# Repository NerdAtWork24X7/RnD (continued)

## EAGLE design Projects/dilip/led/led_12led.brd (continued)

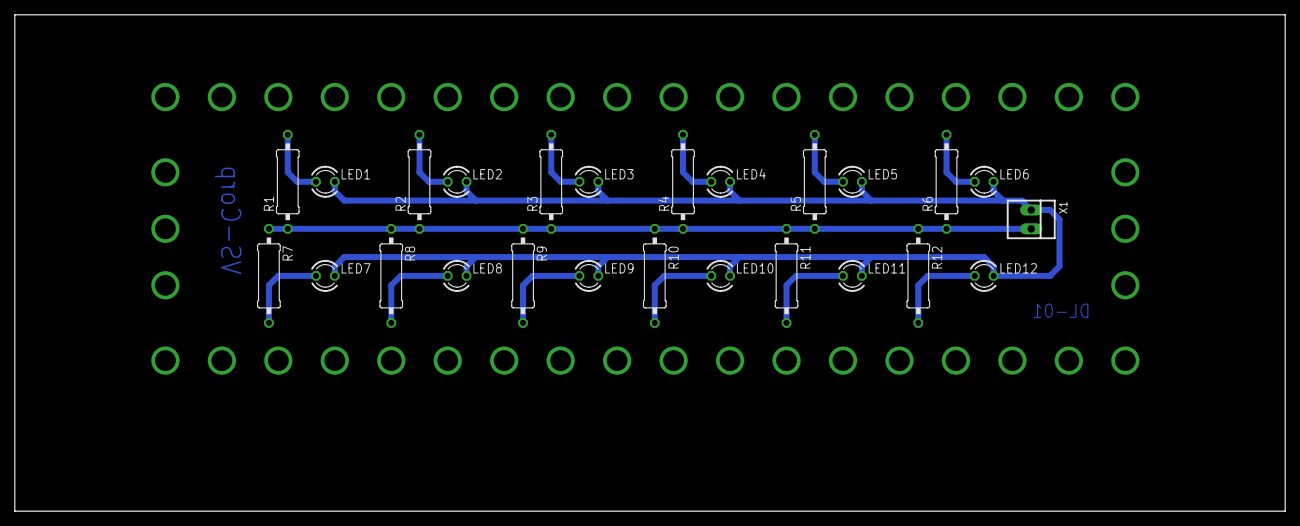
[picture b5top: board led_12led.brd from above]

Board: 2 copper layers, 171.4 x 67.0 mm, 25 parts (0 on the bottom side), 14 nets.

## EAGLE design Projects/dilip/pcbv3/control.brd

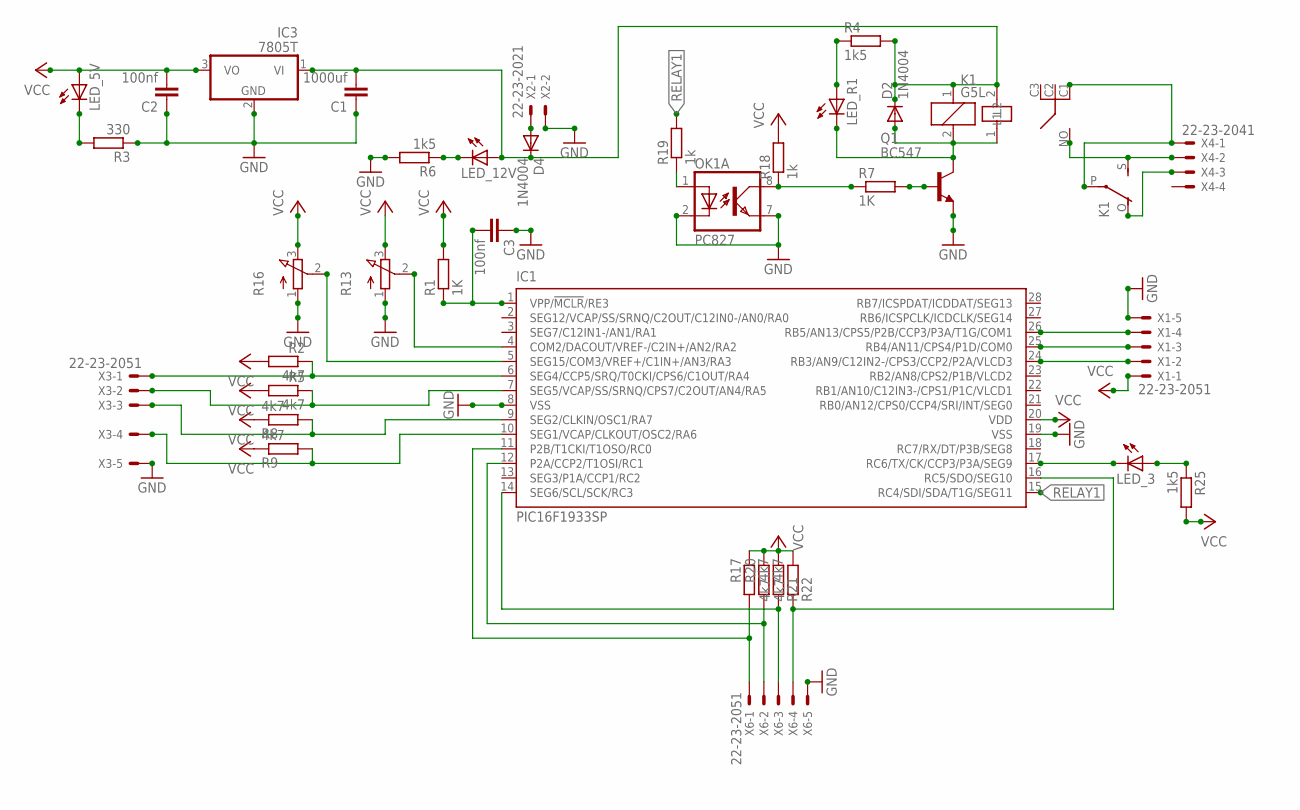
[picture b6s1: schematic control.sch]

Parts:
C1: 1000uf; C5B2.5
C2, C3: 100nf; C2.5-6
D2, D4: 1N4004; DO41-10
IC1: PIC16F1933SP; DIL28-3
IC3: 7805T; TO220H
K1: G5L; G5LE
LED_3, LED_5V, LED_12V: LED3MM
LED_R1: LED3MM
OK1: PC827; DIL08
Q1: BC547; TO92-EBC
R1, R7: 1K; 0207/10
R2, R5, R8, R9, R17, R20, R21, R22: 4k7; 0207/10
R3: 330; 0207/10
R4, R6, R25: 1k5; 0207/10
R13, R16: 3RP/1610N
R18, R19: 1k; 0207/10
U$1: RL703
X1, X3, X6: 22-23-2051
X2: 22-23-2021
X4: 22-23-2041

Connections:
GND: C1.1, C2.1, C3.1, IC1.8 (VSS), IC1.19 (VSS), IC3.2 (GND), OK1.2 (C), OK1.7 (EMIT), Q1.E, R3.1, R6.2, R13.1 (A), R16.1 (A), X1.5, X2.2, X3.5, X6.5
unnamed: IC1.7 (SEG5/VCAP/SS/SRNQ/CPS7/C2OUT/AN4/RA5), R5.1, X3.2
unnamed: C3.2, IC1.1 (VPP/!MCLR!/RE3), R1.1
unnamed: IC1.4 (COM2/DACOUT/VREF-/C2IN+/AN2/RA2), R13.2 (S)
unnamed: IC1.5 (SEG15/COM3/VREF+/C1IN+/AN3/RA3), R16.2 (S)
unnamed: IC1.25 (RB4/AN11/CPS4/P1D/COM0), X1.3
unnamed: IC1.6 (SEG4/CCP5/SRQ/T0CKI/CPS6/C1OUT/RA4), R2.1, X3.1
unnamed: IC1.9 (SEG2/CLKIN/OSC1/RA7), R8.2, X3.3
unnamed: IC1.10 (SEG1/VCAP/CLKOUT/OSC2/RA6), R9.2, X3.4
unnamed: IC1.14 (SEG6/SCL/SCK/RC3), R21.1, X6.3
unnamed: Q1.B, R7.2
unnamed: D2.A, K1.2, LED_R1.K (C), Q1.C, U$1.1 (L2)
unnamed: IC1.11 (P2B/T1CKI/T1OSO/RC0), R17.2, X6.1
unnamed: IC1.24 (RB3/AN9/C12IN2-/CPS3/CCP2/P2A/VLCD3), X1.2
unnamed: IC1.12 (P2A/CCP2/T1OSI/RC1), R20.2, X6.2
unnamed: K1.S, U$1.NO, X4.2
unnamed: K1.P, U$1.C1, X4.1
unnamed: K1.O, X4.3
unnamed: D4.A, X2.1
unnamed: LED_5V.K (C), R3.2
unnamed: IC1.26 (RB5/AN13/CPS5/P2B/CCP3/P3A/T1G/COM1), X1.4
unnamed: LED_R1.A, R4.1
unnamed: LED_12V.K (C), R6.1
unnamed: C1.2, D2.C, D4.C, IC3.1 (VI), K1.1, LED_12V.A, R4.2, U$1.2 (L1)
unnamed: OK1.8 (COL), R7.1, R18.1
unnamed: OK1.1 (A), R19.1
unnamed: IC1.16 (RC5/SDO/SEG10), R22.1, X6.4
unnamed: LED_3.A, R25.1
unnamed: IC1.17 (RC6/TX/CK/CCP3/P3A/SEG9), LED_3.K (C)
RELAY1: IC1.15 (RC4/SDI/SDA/T1G/SEG11), R19.2
VCC: C2.2, IC1.20 (VDD), IC3.3 (VO), LED_5V.A, R1.2, R2.2, R5.2, R8.1, R9.1, R13.3 (E), R16.3 (E), R17.1, R18.2, R20.1, R21.2, R22.2, R25.2, X1.1

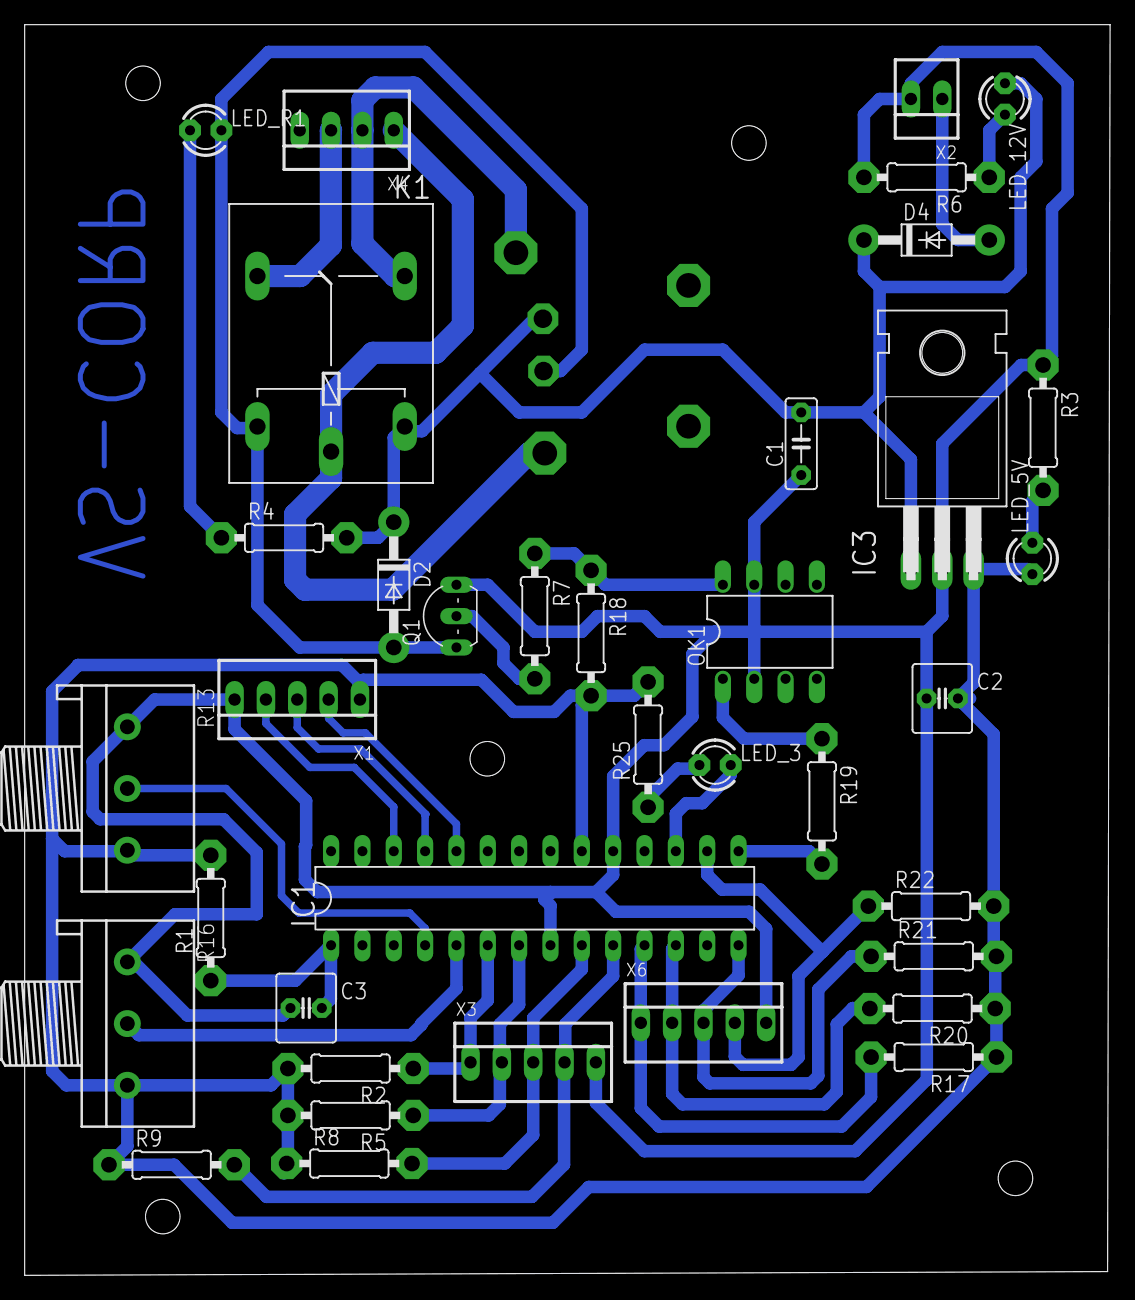
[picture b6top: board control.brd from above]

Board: 2 copper layers, 88.0 x 101.3 mm, 38 parts (0 on the bottom side), 31 nets.

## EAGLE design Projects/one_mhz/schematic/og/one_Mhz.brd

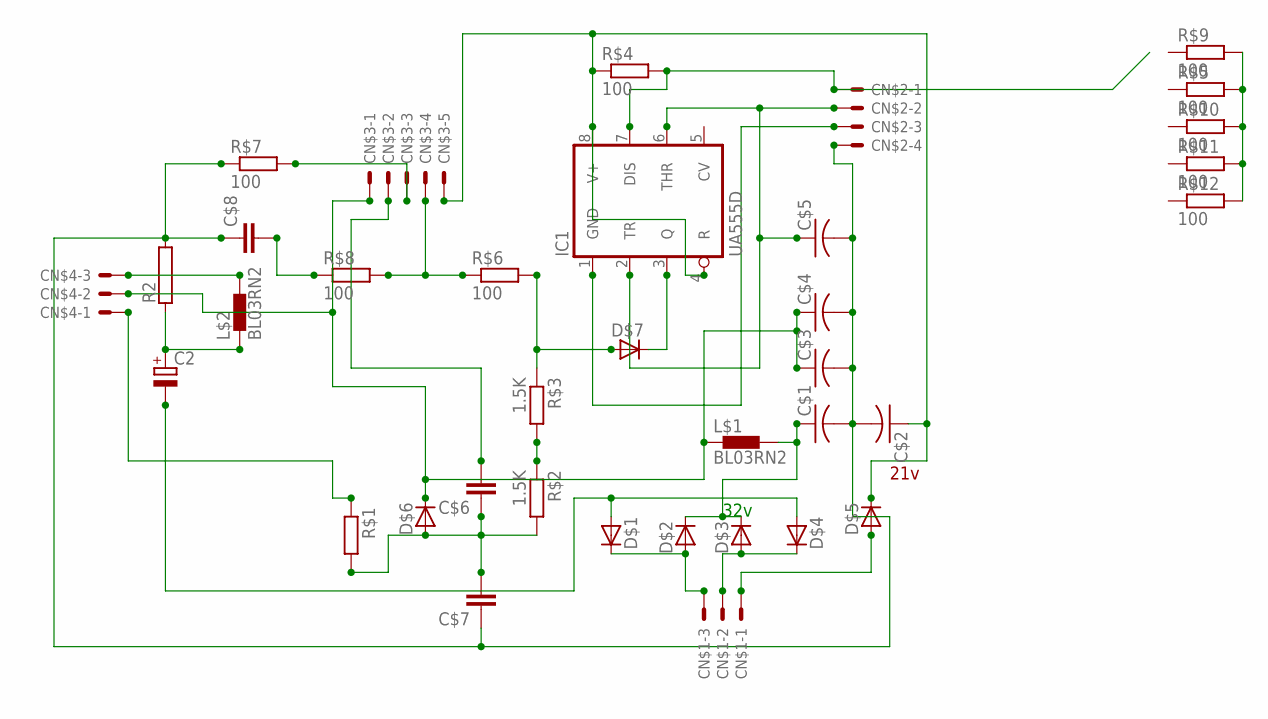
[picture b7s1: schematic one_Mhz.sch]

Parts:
C2: CPOL-EUSANYO_H; SANYO-OSCON_H
C$1, C$2: C-US050-075X075; C050-075X075
C$3, C$4, C$5: C-US025-050X050; C025-050X050
C$6, C$7: C7.5/3; C7.5B3
C$8: C2.5/5; C2.5-5
CN$1, CN$4: KK-156-3
CN$2: KK-156-4
CN$3: KK-156-5
D$1, D$2, D$3, D$4, D$5, D$6, D$7: D-SOD-87; SOD87
IC1: UA555D; SO08
L$1, L$2: BL03RN2
R2: RAC01; AC01
R$1: R-EU_R0603; R0603
R$2, R$3: 1.5K; R0603
R$4, R$5, R$6, R$7, R$8, R$9, R$10, R$11, R$12: 100; R0603

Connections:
unnamed: C$3.1, C$4.1, CN$3.1, CN$4.2, D$6.1 (C), L$1.1
unnamed: CN$1.2, D$3.2 (A), D$4.1 (C)
unnamed: CN$1.3, D$1.1 (C), D$2.2 (A)
unnamed: C2.-, D$1.2 (A), D$4.2 (A)
unnamed: CN$1.1, D$5.2 (A)
unnamed: C$1.2, C$2.2, C$3.2, C$4.2, C$5.2, C$7.1, C$8.1, CN$2.4, R2.2, R$7.1
unnamed: R$2.1, R$3.2
unnamed: D$7.2 (A), R$3.1, R$6.2
unnamed: D$7.1 (C), IC1.3 (Q)
unnamed: CN$3.4, R$6.1, R$8.2
unnamed: C$8.2, R$8.1
unnamed: C$5.1, CN$2.2, IC1.2 (TR), IC1.6 (THR)
unnamed: CN$3.3, R$7.2
unnamed: CN$4.3, L$2.2
unnamed: C2.+, L$2.1, R2.1
unnamed: R$5.2, R$9.2, R$10.2, R$11.2, R$12.2
unnamed: C$6.2, CN$3.2
unnamed: C$6.1, C$7.2, D$6.2 (A), R$1.2, R$2.2
unnamed: C$1.1, D$2.1 (C), D$3.1 (C), L$1.2
unnamed: C$2.1, CN$3.5, D$5.1 (C), IC1.4 (R), IC1.8 (V+), R$4.1
unnamed: CN$4.1, R$1.1
unnamed: CN$2.1, IC1.7 (DIS), R$4.2
unnamed: CN$2.3, IC1.1 (GND)

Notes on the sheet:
21v
32v

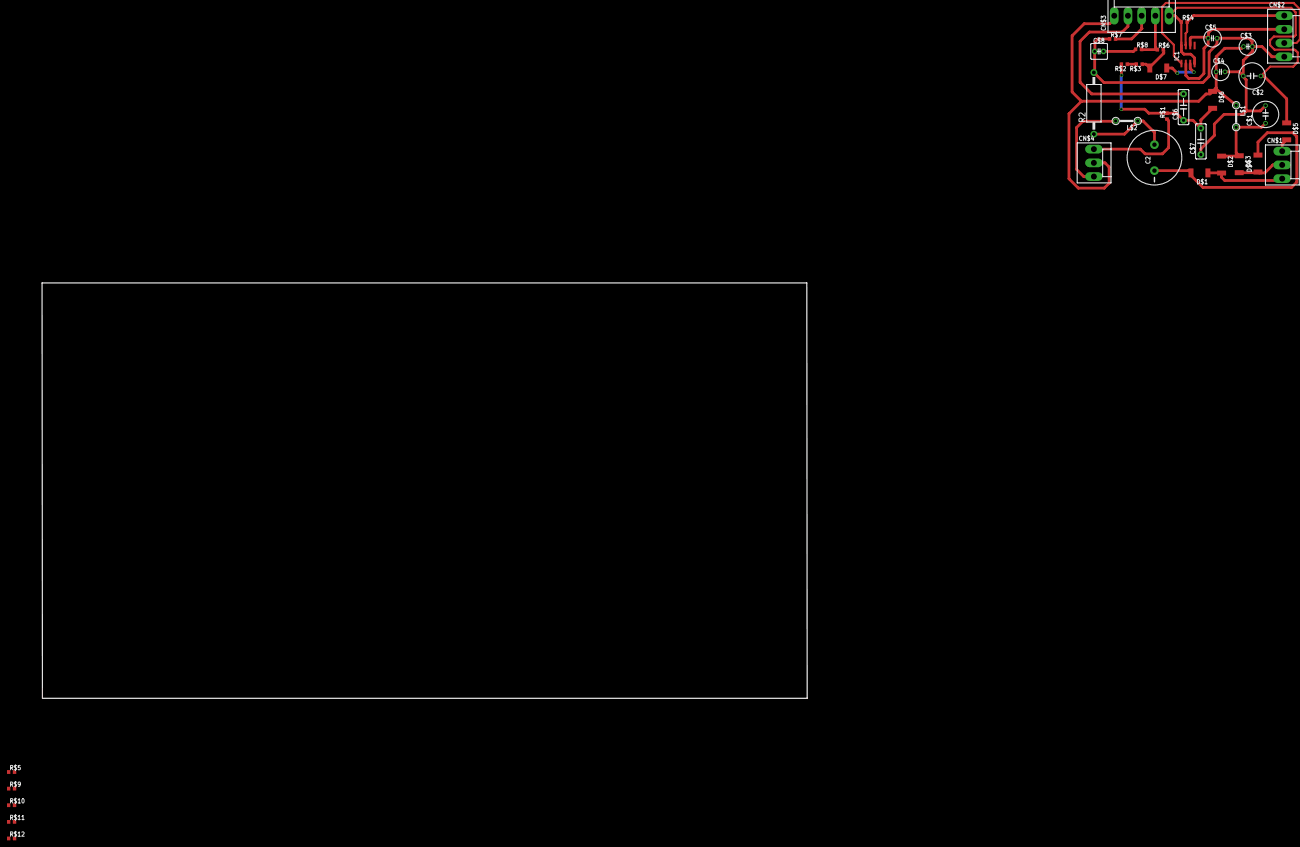
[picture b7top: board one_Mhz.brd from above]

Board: 2 copper layers, 36 parts (0 on the bottom side), 23 nets.

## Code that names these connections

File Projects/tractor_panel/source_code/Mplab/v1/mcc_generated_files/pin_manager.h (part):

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// get/set channel_AN0 aliases
#define channel_AN0_TRIS                 TRISAbits.TRISA0
#define channel_AN0_LAT                  LATAbits.LATA0
#define channel_AN0_PORT                 PORTAbits.RA0
#define channel_AN0_ANS                  ANCON0bits.ANSEL0
#define channel_AN0_SetHigh()            do { LATAbits.LATA0 = 1; } while(0)
#define channel_AN0_SetLow()             do { LATAbits.LATA0 = 0; } while(0)
#define channel_AN0_Toggle()             do { LATAbits.LATA0 = ~LATAbits.LATA0; } while(0)
#define channel_AN0_GetValue()           PORTAbits.RA0
#define channel_AN0_SetDigitalInput()    do { TRISAbits.TRISA0 = 1; } while(0)
#define channel_AN0_SetDigitalOutput()   do { TRISAbits.TRISA0 = 0; } while(0)
#define channel_AN0_SetAnalogMode()      do { ANCON0bits.ANSEL0 = 1; } while(0)
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// get/set channel_AN1 aliases
#define channel_AN1_TRIS                 TRISAbits.TRISA1
#define channel_AN1_LAT                  LATAbits.LATA1
#define channel_AN1_PORT                 PORTAbits.RA1
#define channel_AN1_ANS                  ANCON0bits.ANSEL1
#define channel_AN1_SetHigh()            do { LATAbits.LATA1 = 1; } while(0)
#define channel_AN1_SetLow()             do { LATAbits.LATA1 = 0; } while(0)
#define channel_AN1_Toggle()             do { LATAbits.LATA1 = ~LATAbits.LATA1; } while(0)
#define channel_AN1_GetValue()           PORTAbits.RA1
#define channel_AN1_SetDigitalInput()    do { TRISAbits.TRISA1 = 1; } while(0)
#define channel_AN1_SetDigitalOutput()   do { TRISAbits.TRISA1 = 0; } while(0)
#define channel_AN1_SetAnalogMode()      do { ANCON0bits.ANSEL1 = 1; } while(0)
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// get/set channel_AN2 aliases
#define channel_AN2_TRIS                 TRISAbits.TRISA2
#define channel_AN2_LAT                  LATAbits.LATA2
#define channel_AN2_PORT                 PORTAbits.RA2
#define channel_AN2_ANS                  ANCON0bits.ANSEL2
#define channel_AN2_SetHigh()            do { LATAbits.LATA2 = 1; } while(0)
#define channel_AN2_SetLow()             do { LATAbits.LATA2 = 0; } while(0)
#define channel_AN2_Toggle()             do { LATAbits.LATA2 = ~LATAbits.LATA2; } while(0)
#define channel_AN2_GetValue()           PORTAbits.RA2
#define channel_AN2_SetDigitalInput()    do { TRISAbits.TRISA2 = 1; } while(0)
#define channel_AN2_SetDigitalOutput()   do { TRISAbits.TRISA2 = 0; } while(0)
#define channel_AN2_SetAnalogMode()      do { ANCON0bits.ANSEL2 = 1; } while(0)
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// get/set channel_AN3 aliases
#define channel_AN3_TRIS                 TRISAbits.TRISA3
#define channel_AN3_LAT                  LATAbits.LATA3
#define channel_AN3_PORT                 PORTAbits.RA3
#define channel_AN3_ANS                  ANCON0bits.ANSEL3
#define channel_AN3_SetHigh()            do { LATAbits.LATA3 = 1; } while(0)
#define channel_AN3_SetLow()             do { LATAbits.LATA3 = 0; } while(0)
#define channel_AN3_Toggle()             do { LATAbits.LATA3 = ~LATAbits.LATA3; } while(0)
#define channel_AN3_GetValue()           PORTAbits.RA3
#define channel_AN3_SetDigitalInput()    do { TRISAbits.TRISA3 = 1; } while(0)
#define channel_AN3_SetDigitalOutput()   do { TRISAbits.TRISA3 = 0; } while(0)
#define channel_AN3_SetAnalogMode()      do { ANCON0bits.ANSEL3 = 1; } while(0)
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// get/set channel_AN4 aliases
#define channel_AN4_TRIS                 TRISAbits.TRISA5
#define channel_AN4_LAT                  LATAbits.LATA5
#define channel_AN4_PORT                 PORTAbits.RA5
#define channel_AN4_ANS                  ANCON0bits.ANSEL4
#define channel_AN4_SetHigh()            do { LATAbits.LATA5 = 1; } while(0)
#define channel_AN4_SetLow()             do { LATAbits.LATA5 = 0; } while(0)
#define channel_AN4_Toggle()             do { LATAbits.LATA5 = ~LATAbits.LATA5; } while(0)
#define channel_AN4_GetValue()           PORTAbits.RA5
#define channel_AN4_SetDigitalInput()    do { TRISAbits.TRISA5 = 1; } while(0)
#define channel_AN4_SetDigitalOutput()   do { TRISAbits.TRISA5 = 0; } while(0)
#define channel_AN4_SetAnalogMode()      do { ANCON0bits.ANSEL4 = 1; } while(0)
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// get/set IO_RB0 aliases
#define IO_RB0_TRIS                 TRISBbits.TRISB0
#define IO_RB0_LAT                  LATBbits.LATB0
#define IO_RB0_PORT                 PORTBbits.RB0
#define IO_RB0_WPU                  WPUBbits.WPUB0
#define IO_RB0_ANS                  ANCON1bits.ANSEL10
#define IO_RB0_SetHigh()            do { LATBbits.LATB0 = 1; } while(0)
#define IO_RB0_SetLow()             do { LATBbits.LATB0 = 0; } while(0)
#define IO_RB0_Toggle()             do { LATBbits.LATB0 = ~LATBbits.LATB0; } while(0)
#define IO_RB0_GetValue()           PORTBbits.RB0
#define IO_RB0_SetDigitalInput()    do { TRISBbits.TRISB0 = 1; } while(0)
#define IO_RB0_SetDigitalOutput()   do { TRISBbits.TRISB0 = 0; } while(0)
#define IO_RB0_SetPullup()          do { WPUBbits.WPUB0 = 1; } while(0)
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// get/set IO_RB1 aliases
#define IO_RB1_TRIS                 TRISBbits.TRISB1
#define IO_RB1_LAT                  LATBbits.LATB1
#define IO_RB1_PORT                 PORTBbits.RB1
#define IO_RB1_WPU                  WPUBbits.WPUB1
#define IO_RB1_ANS                  ANCON1bits.ANSEL8
#define IO_RB1_SetHigh()            do { LATBbits.LATB1 = 1; } while(0)
#define IO_RB1_SetLow()             do { LATBbits.LATB1 = 0; } while(0)
#define IO_RB1_Toggle()             do { LATBbits.LATB1 = ~LATBbits.LATB1; } while(0)
#define IO_RB1_GetValue()           PORTBbits.RB1
#define IO_RB1_SetDigitalInput()    do { TRISBbits.TRISB1 = 1; } while(0)
#define IO_RB1_SetDigitalOutput()   do { TRISBbits.TRISB1 = 0; } while(0)
#define IO_RB1_SetPullup()          do { WPUBbits.WPUB1 = 1; } while(0)
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// get/set IO_RB2 aliases
#define IO_RB2_TRIS                 TRISBbits.TRISB2
#define IO_RB2_LAT                  LATBbits.LATB2
#define IO_RB2_PORT                 PORTBbits.RB2
#define IO_RB2_WPU                  WPUBbits.WPUB2
#define IO_RB2_SetHigh()            do { LATBbits.LATB2 = 1; } while(0)
#define IO_RB2_SetLow()             do { LATBbits.LATB2 = 0; } while(0)
#define IO_RB2_Toggle()             do { LATBbits.LATB2 = ~LATBbits.LATB2; } while(0)
#define IO_RB2_GetValue()           PORTBbits.RB2
#define IO_RB2_SetDigitalInput()    do { TRISBbits.TRISB2 = 1; } while(0)
#define IO_RB2_SetDigitalOutput()   do { TRISBbits.TRISB2 = 0; } while(0)
#define IO_RB2_SetPullup()          do { WPUBbits.WPUB2 = 1; } while(0)
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// get/set IO_RB3 aliases
#define IO_RB3_TRIS                 TRISBbits.TRISB3
#define IO_RB3_LAT                  LATBbits.LATB3
#define IO_RB3_PORT                 PORTBbits.RB3
#define IO_RB3_WPU                  WPUBbits.WPUB3
#define IO_RB3_SetHigh()            do { LATBbits.LATB3 = 1; } while(0)
#define IO_RB3_SetLow()             do { LATBbits.LATB3 = 0; } while(0)
#define IO_RB3_Toggle()             do { LATBbits.LATB3 = ~LATBbits.LATB3; } while(0)
#define IO_RB3_GetValue()           PORTBbits.RB3
#define IO_RB3_SetDigitalInput()    do { TRISBbits.TRISB3 = 1; } while(0)
#define IO_RB3_SetDigitalOutput()   do { TRISBbits.TRISB3 = 0; } while(0)
#define IO_RB3_SetPullup()          do { WPUBbits.WPUB3 = 1; } while(0)
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// get/set IO_RC0 aliases
#define IO_RC0_TRIS                 TRISCbits.TRISC0
#define IO_RC0_LAT                  LATCbits.LATC0
#define IO_RC0_PORT                 PORTCbits.RC0
#define IO_RC0_SetHigh()            do { LATCbits.LATC0 = 1; } while(0)
#define IO_RC0_SetLow()             do { LATCbits.LATC0 = 0; } while(0)
#define IO_RC0_Toggle()             do { LATCbits.LATC0 = ~LATCbits.LATC0; } while(0)
#define IO_RC0_GetValue()           PORTCbits.RC0
#define IO_RC0_SetDigitalInput()    do { TRISCbits.TRISC0 = 1; } while(0)
#define IO_RC0_SetDigitalOutput()   do { TRISCbits.TRISC0 = 0; } while(0)

// get/set IO_RC1 aliases
#define IO_RC1_TRIS                 TRISCbits.TRISC1
#define IO_RC1_LAT                  LATCbits.LATC1
#define IO_RC1_PORT                 PORTCbits.RC1
#define IO_RC1_SetHigh()            do { LATCbits.LATC1 = 1; } while(0)
#define IO_RC1_SetLow()             do { LATCbits.LATC1 = 0; } while(0)
#define IO_RC1_Toggle()             do { LATCbits.LATC1 = ~LATCbits.LATC1; } while(0)
#define IO_RC1_GetValue()           PORTCbits.RC1
#define IO_RC1_SetDigitalInput()    do { TRISCbits.TRISC1 = 1; } while(0)
#define IO_RC1_SetDigitalOutput()   do { TRISCbits.TRISC1 = 0; } while(0)

// get/set IO_RC2 aliases
#define IO_RC2_TRIS                 TRISCbits.TRISC2
#define IO_RC2_LAT                  LATCbits.LATC2
#define IO_RC2_PORT                 PORTCbits.RC2
#define IO_RC2_SetHigh()            do { LATCbits.LATC2 = 1; } while(0)
#define IO_RC2_SetLow()             do { LATCbits.LATC2 = 0; } while(0)
#define IO_RC2_Toggle()             do { LATCbits.LATC2 = ~LATCbits.LATC2; } while(0)
#define IO_RC2_GetValue()           PORTCbits.RC2
#define IO_RC2_SetDigitalInput()    do { TRISCbits.TRISC2 = 1; } while(0)
#define IO_RC2_SetDigitalOutput()   do { TRISCbits.TRISC2 = 0; } while(0)

// get/set IO_RC4 aliases
#define IO_RC4_TRIS                 TRISCbits.TRISC4
#define IO_RC4_LAT                  LATCbits.LATC4
#define IO_RC4_PORT                 PORTCbits.RC4
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
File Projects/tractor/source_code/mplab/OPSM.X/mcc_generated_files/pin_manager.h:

#ifndef PIN_MANAGER_H
#define PIN_MANAGER_H

#define INPUT   1
#define OUTPUT  0

#define HIGH    1
#define LOW     0

#define ANALOG      1
#define DIGITAL     0

#define PULL_UP_ENABLED      1
#define PULL_UP_DISABLED     0

// get/set BUZZER aliases
#define BUZZER_TRIS                 TRISAbits.TRISA2
#define BUZZER_LAT                  LATAbits.LATA2
#define BUZZER                      PORTAbits.RA2
#define BUZZER_WPU                  WPUAbits.WPUA2
#define BUZZER_ANS                  ANSELAbits.ANSA2
#define BUZZER_SetHigh()            do { LATAbits.LATA2 = 1; } while(0)
#define BUZZER_SetLow()             do { LATAbits.LATA2 = 0; } while(0)
#define BUZZER_Toggle()             do { LATAbits.LATA2 = ~LATAbits.LATA2; } while(0)
#define BUZZER_GetValue()           PORTAbits.RA2
#define BUZZER_SetDigitalInput()    do { TRISAbits.TRISA2 = 1; } while(0)
#define BUZZER_SetDigitalOutput()   do { TRISAbits.TRISA2 = 0; } while(0)
#define BUZZER_SetPullup()          do { WPUAbits.WPUA2 = 1; } while(0)
#define BUZZER_ResetPullup()        do { WPUAbits.WPUA2 = 0; } while(0)
#define BUZZER_SetAnalogMode()      do { ANSELAbits.ANSA2 = 1; } while(0)
#define BUZZER_SetDigitalMode()     do { ANSELAbits.ANSA2 = 0; } while(0)

// get/set RELAY_STR aliases
#define RELAY_STR_TRIS                 TRISAbits.TRISA4
#define RELAY_STR_LAT                  LATAbits.LATA4
#define RELAY_STR                      PORTAbits.RA4
#define RELAY_STR_WPU                  WPUAbits.WPUA4
#define RELAY_STR_ANS                  ANSELAbits.ANSA4
#define RELAY_STR_SetHigh()            do { LATAbits.LATA4 = 1; } while(0)
#define RELAY_STR_SetLow()             do { LATAbits.LATA4 = 0; } while(0)
#define RELAY_STR_Toggle()             do { LATAbits.LATA4 = ~LATAbits.LATA4; } while(0)
#define RELAY_STR_GetValue()           PORTAbits.RA4
#define RELAY_STR_SetDigitalInput()    do { TRISAbits.TRISA4 = 1; } while(0)
#define RELAY_STR_SetDigitalOutput()   do { TRISAbits.TRISA4 = 0; } while(0)
#define RELAY_STR_SetPullup()          do { WPUAbits.WPUA4 = 1; } while(0)
#define RELAY_STR_ResetPullup()        do { WPUAbits.WPUA4 = 0; } while(0)
#define RELAY_STR_SetAnalogMode()      do { ANSELAbits.ANSA4 = 1; } while(0)
#define RELAY_STR_SetDigitalMode()     do { ANSELAbits.ANSA4 = 0; } while(0)

// get/set ENGINE_SENSE aliases
#define ENGINE_SENSE_TRIS                 TRISCbits.TRISC0
#define ENGINE_SENSE_LAT                  LATCbits.LATC0
#define ENGINE_SENSE                      PORTCbits.RC0
#define ENGINE_SENSE_ANS                  ANSELCbits.ANSC0
#define ENGINE_SENSE_SetHigh()            do { LATCbits.LATC0 = 1; } while(0)
#define ENGINE_SENSE_SetLow()             do { LATCbits.LATC0 = 0; } while(0)
#define ENGINE_SENSE_Toggle()             do { LATCbits.LATC0 = ~LATCbits.LATC0; } while(0)
#define ENGINE_SENSE_GetValue()           PORTCbits.RC0
#define ENGINE_SENSE_SetDigitalInput()    do { TRISCbits.TRISC0 = 1; } while(0)
#define ENGINE_SENSE_SetDigitalOutput()   do { TRISCbits.TRISC0 = 0; } while(0)
#define ENGINE_SENSE_SetAnalogMode()      do { ANSELCbits.ANSC0 = 1; } while(0)
#define ENGINE_SENSE_SetDigitalMode()     do { ANSELCbits.ANSC0 = 0; } while(0)

// get/set HAND_BRAKE aliases
#define HAND_BRAKE_TRIS                 TRISCbits.TRISC1
#define HAND_BRAKE_LAT                  LATCbits.LATC1
#define HAND_BRAKE                      PORTCbits.RC1
#define HAND_BRAKE_ANS                  ANSELCbits.ANSC1
#define HAND_BRAKE_SetHigh()            do { LATCbits.LATC1 = 1; } while(0)
#define HAND_BRAKE_SetLow()             do { LATCbits.LATC1 = 0; } while(0)
#define HAND_BRAKE_Toggle()             do { LATCbits.LATC1 = ~LATCbits.LATC1; } while(0)
#define HAND_BRAKE_GetValue()           PORTCbits.RC1
#define HAND_BRAKE_SetDigitalInput()    do { TRISCbits.TRISC1 = 1; } while(0)
#define HAND_BRAKE_SetDigitalOutput()   do { TRISCbits.TRISC1 = 0; } while(0)
#define HAND_BRAKE_SetAnalogMode()      do { ANSELCbits.ANSC1 = 1; } while(0)
#define HAND_BRAKE_SetDigitalMode()     do { ANSELCbits.ANSC1 = 0; } while(0)

// get/set PTO aliases
#define PTO_TRIS                 TRISCbits.TRISC2
#define PTO_LAT                  LATCbits.LATC2
#define PTO                      PORTCbits.RC2
#define PTO_ANS                  ANSELCbits.ANSC2
#define PTO_SetHigh()            do { LATCbits.LATC2 = 1; } while(0)
#define PTO_SetLow()             do { LATCbits.LATC2 = 0; } while(0)
#define PTO_Toggle()             do { LATCbits.LATC2 = ~LATCbits.LATC2; } while(0)
#define PTO_GetValue()           PORTCbits.RC2
#define PTO_SetDigitalInput()    do { TRISCbits.TRISC2 = 1; } while(0)
#define PTO_SetDigitalOutput()   do { TRISCbits.TRISC2 = 0; } while(0)
#define PTO_SetAnalogMode()      do { ANSELCbits.ANSC2 = 1; } while(0)
#define PTO_SetDigitalMode()     do { ANSELCbits.ANSC2 = 0; } while(0)

// get/set SEAT_SWITCH aliases
#define SEAT_SWITCH_TRIS                 TRISCbits.TRISC3
#define SEAT_SWITCH_LAT                  LATCbits.LATC3
#define SEAT_SWITCH                      PORTCbits.RC3
#define SEAT_SWITCH_ANS                  ANSELCbits.ANSC3
#define SEAT_SWITCH_SetHigh()            do { LATCbits.LATC3 = 1; } while(0)
#define SEAT_SWITCH_SetLow()             do { LATCbits.LATC3 = 0; } while(0)
#define SEAT_SWITCH_Toggle()             do { LATCbits.LATC3 = ~LATCbits.LATC3; } while(0)
#define SEAT_SWITCH_GetValue()           PORTCbits.RC3
#define SEAT_SWITCH_SetDigitalInput()    do { TRISCbits.TRISC3 = 1; } while(0)
#define SEAT_SWITCH_SetDigitalOutput()   do { TRISCbits.TRISC3 = 0; } while(0)
#define SEAT_SWITCH_SetAnalogMode()      do { ANSELCbits.ANSC3 = 1; } while(0)
#define SEAT_SWITCH_SetDigitalMode()     do { ANSELCbits.ANSC3 = 0; } while(0)

// get/set P_IND aliases
#define P_IND_TRIS                 TRISCbits.TRISC4
#define P_IND_LAT                  LATCbits.LATC4
#define P_IND                      PORTCbits.RC4
#define P_IND_SetHigh()            do { LATCbits.LATC4 = 1; } while(0)
#define P_IND_SetLow()             do { LATCbits.LATC4 = 0; } while(0)
#define P_IND_Toggle()             do { LATCbits.LATC4 = ~LATCbits.LATC4; } while(0)
#define P_IND_GetValue()           PORTCbits.RC4
#define P_IND_SetDigitalInput()    do { TRISCbits.TRISC4 = 1; } while(0)
#define P_IND_SetDigitalOutput()   do { TRISCbits.TRISC4 = 0; } while(0)

// get/set RELAY_SOL aliases
#define RELAY_SOL_TRIS                 TRISCbits.TRISC5
#define RELAY_SOL_LAT                  LATCbits.LATC5
#define RELAY_SOL                      PORTCbits.RC5
#define RELAY_SOL_SetHigh()            do { LATCbits.LATC5 = 1; } while(0)
#define RELAY_SOL_SetLow()             do { LATCbits.LATC5 = 0; } while(0)
#define RELAY_SOL_Toggle()             do { LATCbits.LATC5 = ~LATCbits.LATC5; } while(0)
#define RELAY_SOL_GetValue()           PORTCbits.RC5
#define RELAY_SOL_SetDigitalInput()    do { TRISCbits.TRISC5 = 1; } while(0)
#define RELAY_SOL_SetDigitalOutput()   do { TRISCbits.TRISC5 = 0; } while(0)

/**
   @Param
    none
   @Returns
    none
   @Description
    GPIO and peripheral I/O initialization
   @Example
    PIN_MANAGER_Initialize();
 */
void PIN_MANAGER_Initialize (void);

/**
 * @Param
    none
 * @Returns
    none
 * @Description
    Interrupt on Change Handling routine
 * @Example
    PIN_MANAGER_IOC();
 */
void PIN_MANAGER_IOC(void);



#endif // PIN_MANAGER_H
/**
 End of File
*/

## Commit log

2018-11-07 initial version
2018-11-07 ignore file updated
2018-11-18 V2.3 source
2018-12-05 updated v1.5 v1.6 and v2.2
2018-12-05 proteus vile for v1.5 and v1.6
2018-12-12 Python projects
2018-12-16 bug fix in 1.5
2018-12-21 folder structure updated
2018-12-23 tractor v2_4 changed in schematic 12v -> Gnd for contactor and modified src code for delay
2019-01-03 2V4 release
2019-01-05 schematic changes
2019-01-19 Version2.5 modified schematic and code updated
2019-02-16 Final release of 2v5
2019-02-28 v2.5 bug fix
2019-03-10 v2_5 hb fixed
2019-04-19 mod_2v5 state machine
2020-03-14 14-03-2020 commit
2020-08-08 drip irrigation
2020-08-08 latest
2021-07-18 Speech recognistatin
2021-08-25 crypto bot
